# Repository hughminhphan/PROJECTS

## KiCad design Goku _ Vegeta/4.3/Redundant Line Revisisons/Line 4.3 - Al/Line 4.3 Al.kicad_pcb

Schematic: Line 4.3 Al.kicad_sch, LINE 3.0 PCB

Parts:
A1: ALS-PT19; R_1210_3225Metric; PARTREV 5
A2, A3, A4, A5, A6, A7, A8, A9, A10, A11, A12, A13, A14, A15, A16, A17, A18, A19, A20, A21, A22, A23, A24: ALS-PT19; XDCR_ALS-PT19-315C_L177_TR8; PARTREV 5
C1: 0.1uF; C_0402_1005Metric
C2: 10uF; 0805
C3: 4.7uF; C_0805_2012Metric
C4: 0.1uF; C_0805_2012Metric
C5, C6: 22uF; C_0805_2012Metric
C7: 1uF; C_0805_2012Metric
J1, J2, J3, J4: Solder Pad; SolderWirePad_1x01_SMD_1x2mm
LED1, LED2, LED3, LED4, LED5, LED6, LED7, LED8, LED9, LED10, LED11, LED12, LED13, LED14, LED15, LED16, LED17, LED18, LED19, LED20, LED21, LED22, LED23, LED24: JB2835AWT-W-U30GA0000-N0000001; LED_J2835_CRW
R1, R2, R3, R4, R5, R6, R7, R8, R9, R10, R11, R12, R13, R14, R15, R16, R17, R18, R19, R20, R21, R22, R23, R24: 12R; 0805
R25, R26, R27, R28, R29, R30, R31, R32, R33, R34, R35, R36, R37, R38, R39, R40, R41, R42, R43, R44, R45, R46, R47, R48: 330R; 0805
R49, R50, R51, R52, R53, R54, R55, R56, R57, R58, R59, R60, R61, R62, R63, R64, R65, R66, R67, R68, R69, R70, R71, R72, R97, R98, R99, R100, R101, R102, R103, R104, R105, R106, R107, R108: 10k; 0805
R73, R74, R75, R76, R77, R78, R79, R80, R81, R82, R83, R84, R85, R86, R87, R88, R89, R90, R91, R92, R93, R94, R95, R96, R133, R134, R135, R136, R137, R138, R139, R140, R141, R142, R143, R144, R145, R146, R147, R148, R149, R152, R153, R154, R155, R156: 0R; R_1210_3225Metric
R109, R110, R111, R112, R113, R114, R115, R116, R117, R118, R119, R120, R121, R122, R123, R124, R125, R126, R127, R128, R129, R130, R131, R132: 0R; R_0603_1608Metric
R150, R151: 10k; R_0805_2012Metric
R157: 0R; R_0805_2012Metric
U1, U2, U3, U4, U5, U6: LM339; TSSOP-14_W4.4mm
U7: SC0915; MODULE_SC0915; PARTREV 1.9
U8: TPSM33625RDNR; QFN-FCMOD11_RDN_TEX

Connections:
+3V3: A1.1, A2.1, A3.1, A4.1, A5.1, A6.1, A7.1, A8.1, A9.1, A10.1, A11.1, A12.1, A13.1, A14.1, A15.1, A16.1, A17.1, A18.1, A19.1, A20.1, A21.1, A22.1, A23.1, A24.1, C1.2, C2.2, C5.1, C6.1, R1.1, R2.1, R3.1, R4.1, R5.1, R6.1, R7.1, R8.1, R9.1, R10.1, R11.1, R12.1, R13.1, R14.1, R15.1, R16.1, R17.1, R18.1, R19.1, R20.1, R21.1, R22.1, R23.1, R24.1, R49.2, R50.2, R51.2, R52.2, R53.2, R54.2, R55.2, R56.2, R57.2, R58.2, R59.2, R60.2, R61.2, R62.2, R63.2, R64.2, R65.2, R66.2, R67.2, R68.2, R69.2, R70.2, R71.2, R72.2, R97.2, R99.2, R101.2, R103.2, R105.2, R107.2, R109.1, R109.2, R110.1, R110.2, R111.1, R111.2, R112.1, R112.2, R113.1, R113.2, R114.1, R114.2, R115.1, R115.2, R116.1, R116.2, R117.1, R117.2, R118.1, R118.2, R119.1, R119.2, R120.1, R120.2, R121.1, R121.2, R122.1, R122.2, R123.1, R123.2, R124.1, R124.2, R125.1, R125.2, R126.1, R126.2, R127.1, R127.2, R128.1, R128.2, R129.1, R129.2, R130.1, R130.2, R131.1, R131.2, R132.1, R132.2, R150.2, R152.1, R152.2, R153.1, R153.2, R154.1, R154.2, R155.1, R155.2, R156.1, R156.2, U1.3 (V+), U2.3 (V+), U3.3 (V+), U4.3 (V+), U5.3 (V+), U6.3 (V+), U7.39 (VSYS), U8.4 (VOUT)
+15V: C3.1, C4.1, J1.1, U8.2 (EN), U8.3 (VIN)
/SCL: J4.1, U7.2 (GP1)
/SDA: J3.1, U7.1 (GP0)
/SEN1: R49.1, U1.2, U7.29 (GP22)
/SEN2: R50.1, U1.1, U7.31 (GP26)
/SEN3: R51.1, U1.14, U7.32 (GP27)
/SEN4: R52.1, U1.13, U7.34 (GP28)
/SEN5: R53.1, U2.2, U7.6 (GP4)
/SEN6: R54.1, U2.1, U7.7 (GP5)
/SEN7: R55.1, U2.14, U7.5 (GP3)
/SEN8: R56.1, U2.13, U7.4 (GP2)
/SEN9: R57.1, U3.2, U7.9 (GP6)
/SEN10: R58.1, U3.1, U7.10 (GP7)
/SEN11: R59.1, U3.14, U7.11 (GP8)
/SEN12: R60.1, U3.13, U7.12 (GP9)
/SEN13: R61.1, U4.2, U7.14 (GP10)
/SEN14: R62.1, U4.1, U7.15 (GP11)
/SEN15: R63.1, U4.14, U7.16 (GP12)
/SEN16: R64.1, U4.13, U7.17 (GP13)
/SEN17: R65.1, U5.2, U7.19 (GP14)
/SEN18: R66.1, U5.1, U7.20 (GP15)
/SEN19: R67.1, U5.14, U7.22 (GP17)
/SEN20: R68.1, U5.13, U7.21 (GP16)
/SEN21: R69.1, U6.2, U7.24 (GP18)
/SEN22: R70.1, U6.1, U7.25 (GP19)
/SEN23: R71.1, U6.14, U7.26 (GP20)
/SEN24: R72.1, U6.13, U7.27 (GP21)
/VREF1: R97.1, R98.2, U1.4 (-), U1.6 (-), U1.8 (-), U1.10 (-)
/VREF2: R99.1, R100.2, U2.4 (-), U2.6 (-), U2.8 (-), U2.10 (-)
/VREF3: R101.1, R102.2, U3.4 (-), U3.6 (-), U3.8 (-), U3.10 (-)
/VREF4: R103.1, R104.2, U4.4 (-), U4.6 (-), U4.8 (-), U4.10 (-)
/VREF5: R105.1, R106.2, U5.4 (-), U5.6 (-), U5.8 (-), U5.10 (-)
/VREF6: R107.1, R108.2, U6.4 (-), U6.6 (-), U6.8 (-), U6.10 (-)
GND: C1.1, C2.1, C3.2, C4.2, C5.2, C6.2, C7.2, J2.1, LED1.1, LED2.1, LED3.1, LED4.1, LED5.1, LED6.1, LED7.1, LED8.1, LED9.1, LED10.1, LED11.1, LED12.1, LED13.1, LED14.1, LED15.1, LED16.1, LED17.1, LED18.1, LED19.1, LED20.1, LED21.1, LED22.1, LED23.1, LED24.1, R25.1, R26.1, R27.1, R28.1, R29.1, R30.1, R31.1, R32.1, R33.1, R34.1, R35.1, R36.1, R37.1, R38.1, R39.1, R40.1, R41.1, R42.1, R43.1, R44.1, R45.1, R46.1, R47.1, R48.1, R73.1, R73.2, R74.1, R74.2, R75.1, R75.2, R76.1, R76.2, R77.1, R77.2, R78.1, R78.2, R79.1, R79.2, R80.1, R80.2, R81.1, R81.2, R82.1, R82.2, R83.1, R83.2, R84.1, R84.2, R85.1, R85.2, R86.1, R86.2, R87.1, R87.2, R88.1, R88.2, R89.1, R89.2, R90.1, R90.2, R91.1, R91.2, R92.1, R92.2, R93.1, R93.2, R94.1, R94.2, R95.1, R95.2, R96.1, R96.2, R98.1, R100.1, R102.1, R104.1, R106.1, R108.1, R133.1, R133.2, R134.1, R134.2, R135.1, R135.2, R136.1, R136.2, R137.1, R137.2, R138.1, R138.2, R139.1, R139.2, R140.1, R140.2, R141.1, R141.2, R142.1, R142.2, R143.1, R143.2, R144.1, R144.2, R145.1, R145.2, R146.1, R146.2, R147.1, R147.2, R148.1, R148.2, R149.1, R149.2, R151.1, R157.1, R157.2, U1.12 (V-), U2.12 (V-), U3.12 (V-), U4.12 (V-), U5.12 (V-), U6.12 (V-), U7.3 (GND), U7.8 (GND), U7.13 (GND), U7.18 (GND), U7.23 (GND), U7.28 (GND), U7.33 (AGND), U7.38 (GND), U7.D2 (GND), U8.10 (GND), U8.11 (RT)
unnamed: LED1.2, R1.2
unnamed: LED2.2, R2.2
unnamed: LED3.2, R3.2
unnamed: LED4.2, R4.2
unnamed: LED5.2, R5.2
unnamed: LED6.2, R6.2
unnamed: LED7.2, R7.2
unnamed: LED8.2, R8.2
unnamed: LED9.2, R9.2
unnamed: LED10.2, R10.2
unnamed: LED11.2, R11.2
unnamed: LED12.2, R12.2
unnamed: LED13.2, R13.2
unnamed: LED14.2, R14.2
unnamed: LED15.2, R15.2
unnamed: LED16.2, R16.2
unnamed: LED17.2, R17.2
unnamed: LED18.2, R18.2
unnamed: LED19.2, R19.2
unnamed: LED20.2, R20.2
unnamed: LED21.2, R21.2
unnamed: LED22.2, R22.2
unnamed: LED23.2, R23.2
unnamed: LED24.2, R24.2
unnamed: A1.2, R25.2, U1.5 (+)
unnamed: A2.2, R26.2, U1.7 (+)
unnamed: A4.2, R28.2, U1.11 (+)
unnamed: A3.2, R27.2, U1.9 (+)
unnamed: A5.2, R29.2, U2.5 (+)
unnamed: A6.2, R30.2, U2.7 (+)
unnamed: A8.2, R32.2, U2.11 (+)
unnamed: A7.2, R31.2, U2.9 (+)
unnamed: A9.2, R33.2, U3.5 (+)
unnamed: A10.2, R34.2, U3.7 (+)
unnamed: A12.2, R36.2, U3.11 (+)
unnamed: A11.2, R35.2, U3.9 (+)
unnamed: A13.2, R37.2, U4.5 (+)
unnamed: A14.2, R38.2, U4.7 (+)
unnamed: A16.2, R40.2, U4.11 (+)
unnamed: A15.2, R39.2, U4.9 (+)
unnamed: A17.2, R41.2, U5.5 (+)
unnamed: A18.2, R42.2, U5.7 (+)
unnamed: A20.2, R44.2, U5.11 (+)
unnamed: A19.2, R43.2, U5.9 (+)
unnamed: A21.2, R45.2, U6.5 (+)
unnamed: A22.2, R46.2, U6.7 (+)
unnamed: A24.2, R48.2, U6.11 (+)
unnamed: A23.2, R47.2, U6.9 (+)
unnamed: R150.1, R151.2, U8.9 (FB)
unnamed: U8.5 (SW), U8.6 (SW)
unnamed: C7.1, U8.8 (VCC)

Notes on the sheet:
NOTES TO SELF
NEXT STEPS: MAYBE: Things that are being tested: - buck converter circuit - potentimeter voltage divider circuit - comparator circuit - leds on 3v3
SENSORS
TUNING
make sure that resistor is 1/4 watt
CONNECTORS
MCU
3V3 BUCK CONVERTER
COMPARATORS

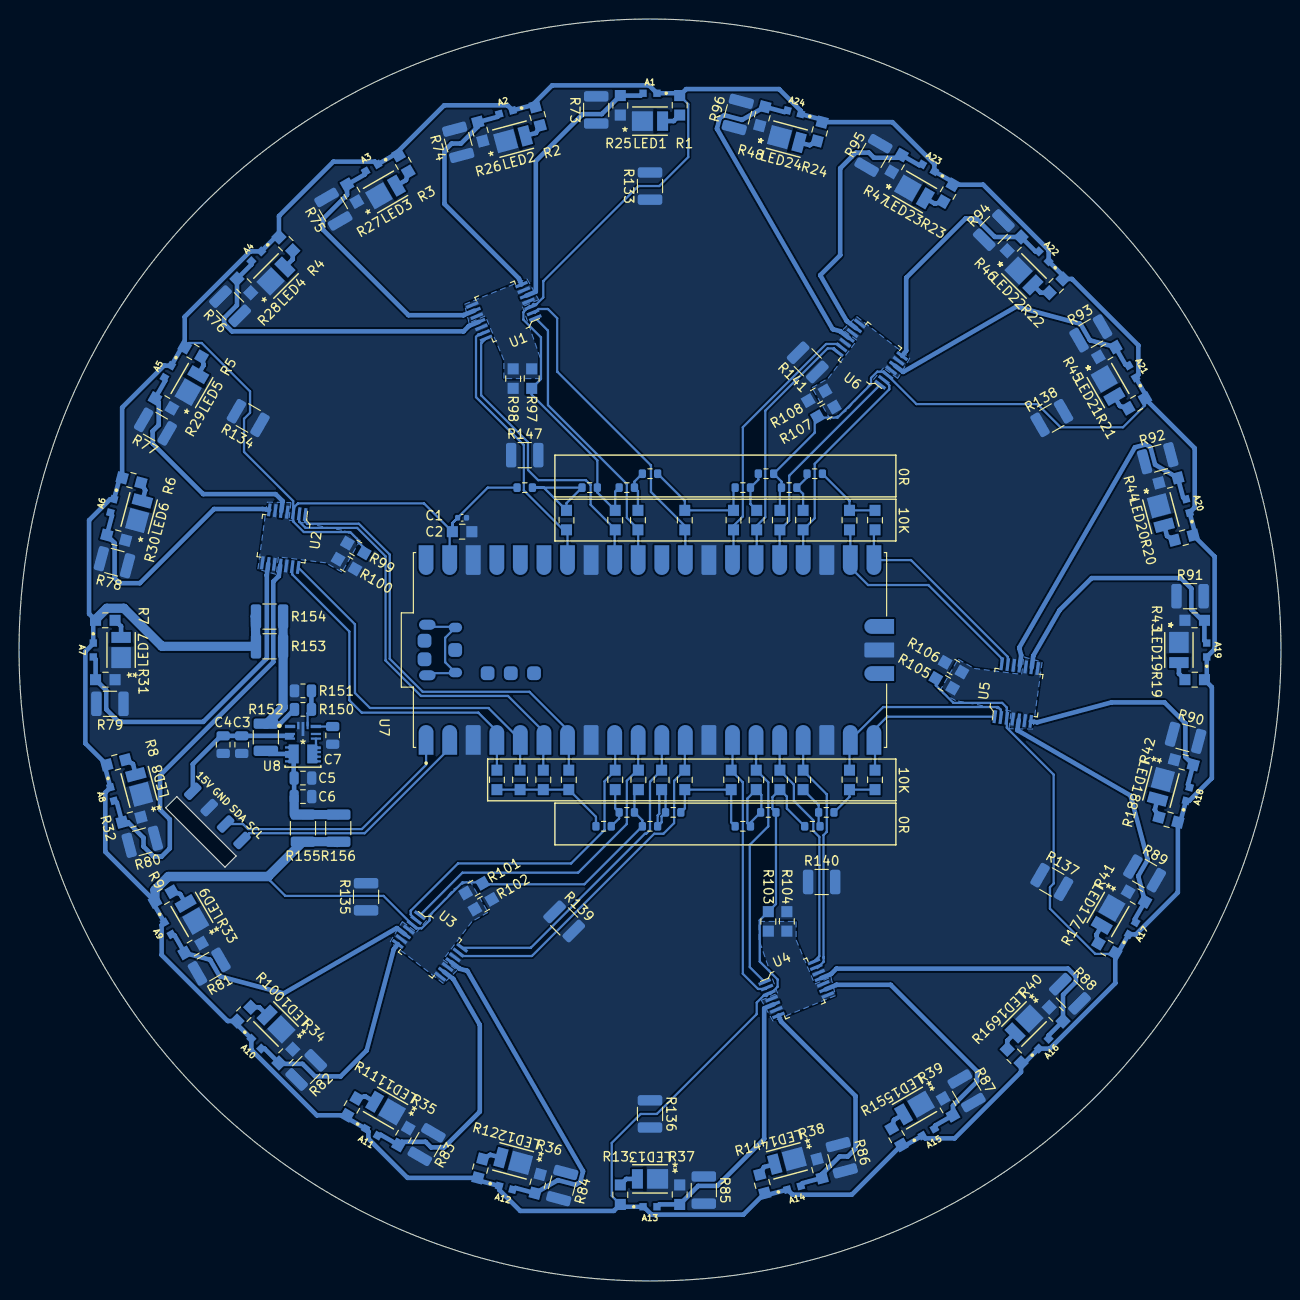
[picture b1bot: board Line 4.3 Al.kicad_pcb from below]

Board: 2 copper layers, 136.0 x 136.0 mm, 208 parts (208 on the bottom side), 86 nets.

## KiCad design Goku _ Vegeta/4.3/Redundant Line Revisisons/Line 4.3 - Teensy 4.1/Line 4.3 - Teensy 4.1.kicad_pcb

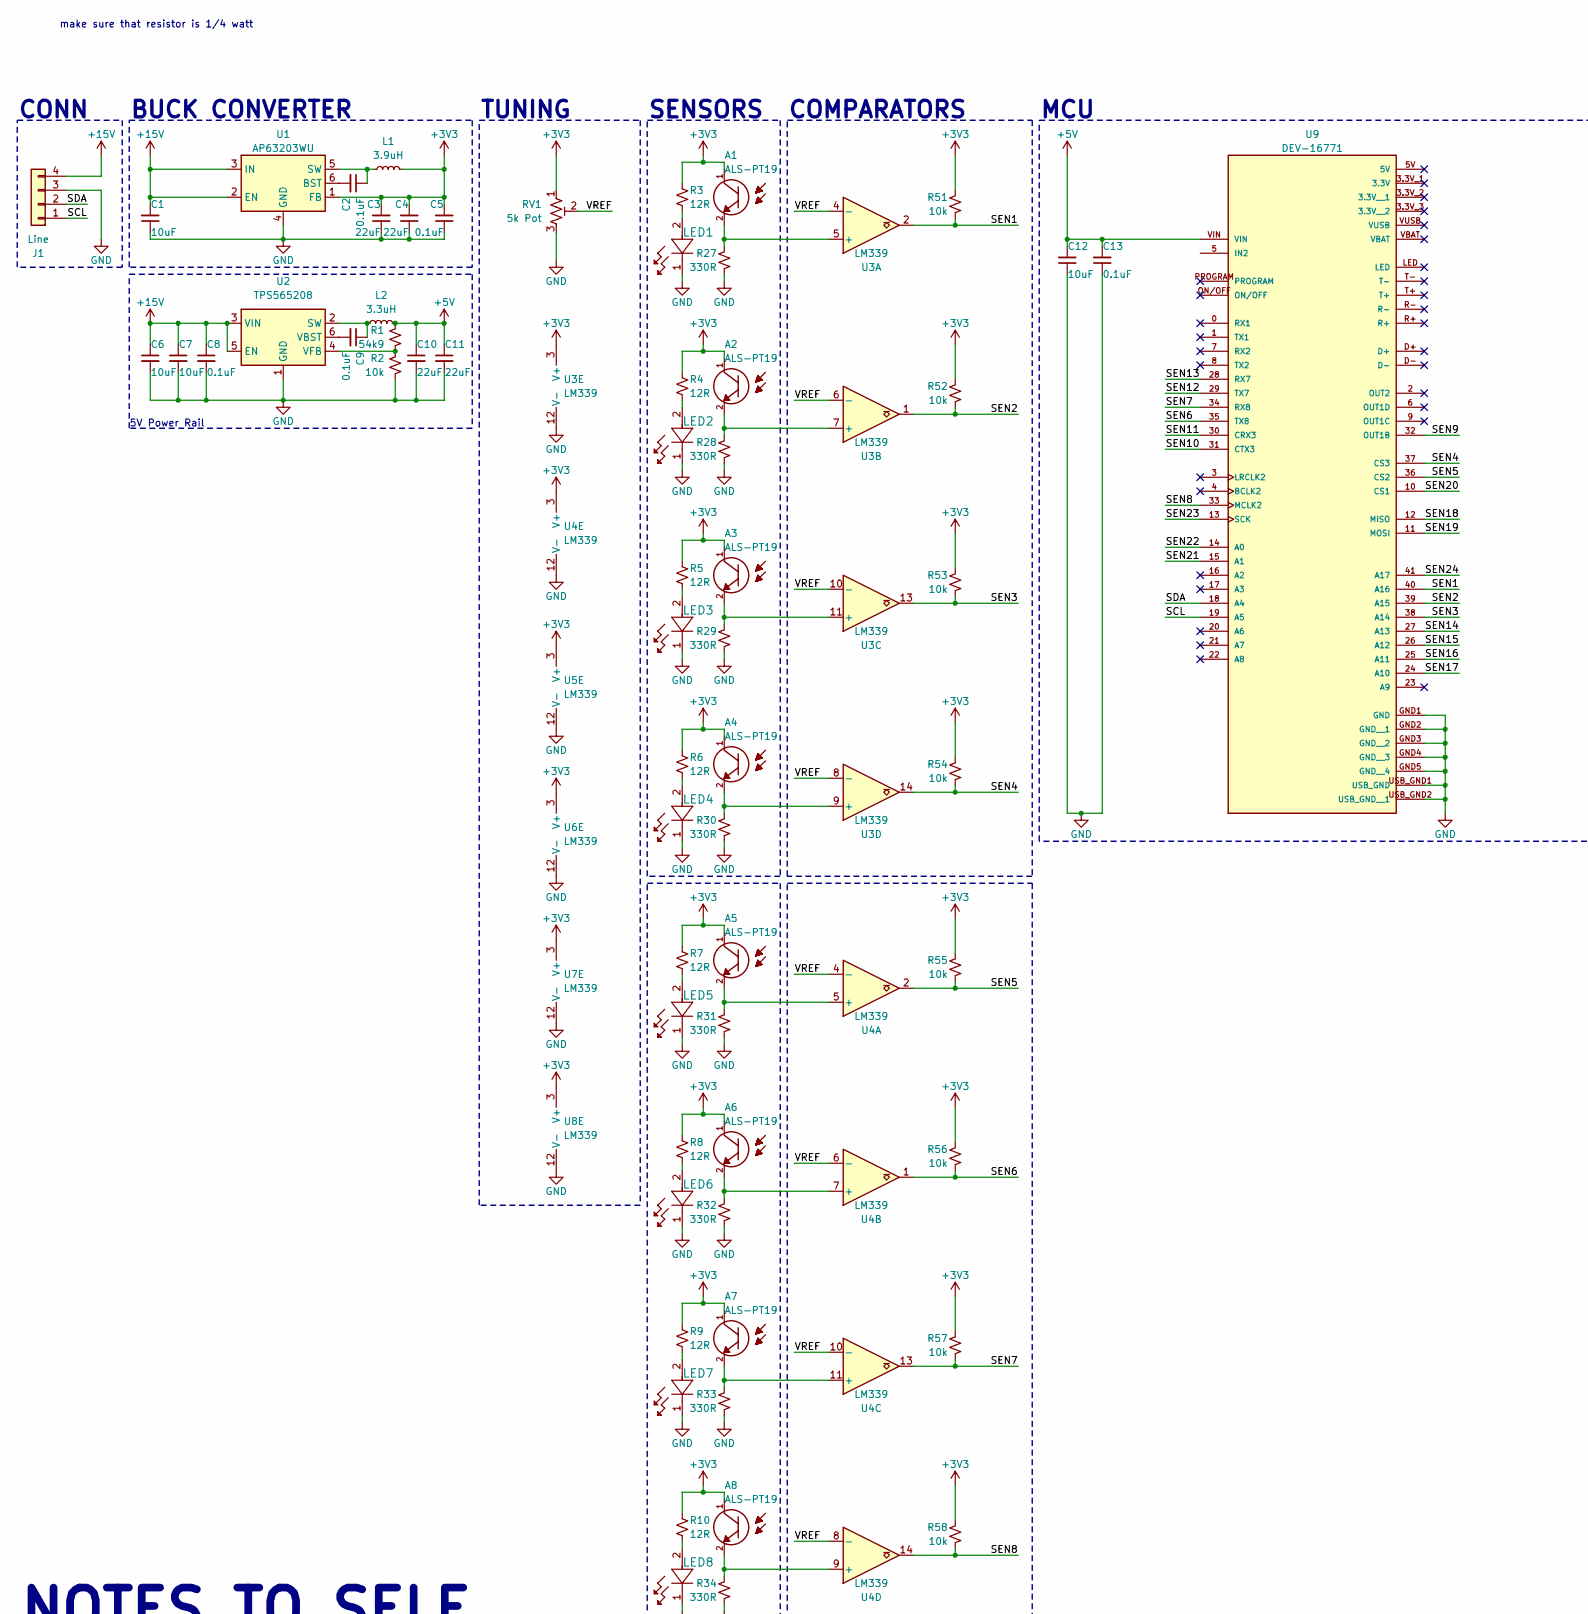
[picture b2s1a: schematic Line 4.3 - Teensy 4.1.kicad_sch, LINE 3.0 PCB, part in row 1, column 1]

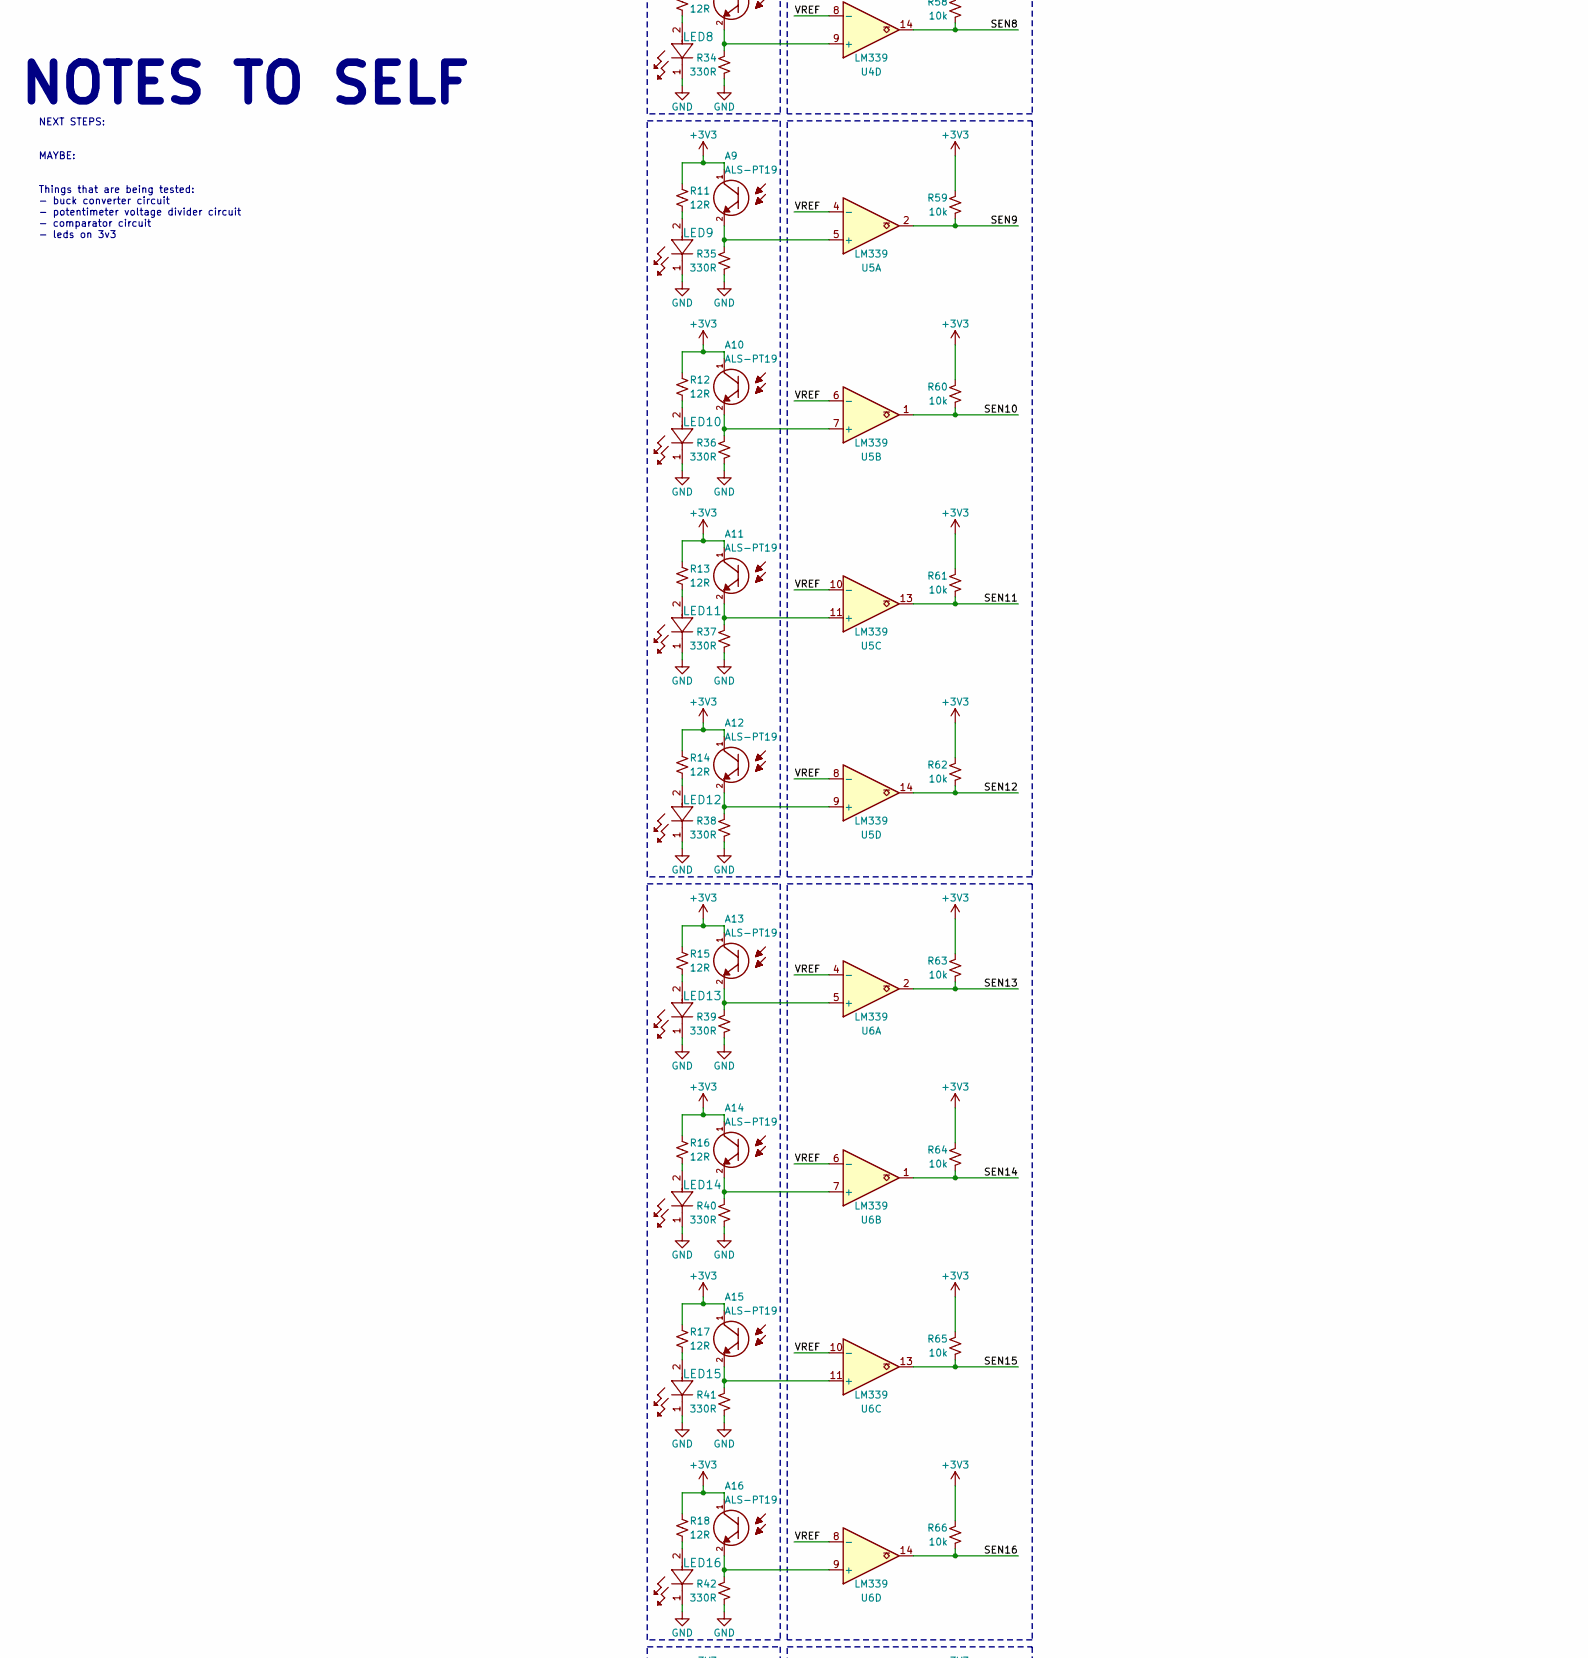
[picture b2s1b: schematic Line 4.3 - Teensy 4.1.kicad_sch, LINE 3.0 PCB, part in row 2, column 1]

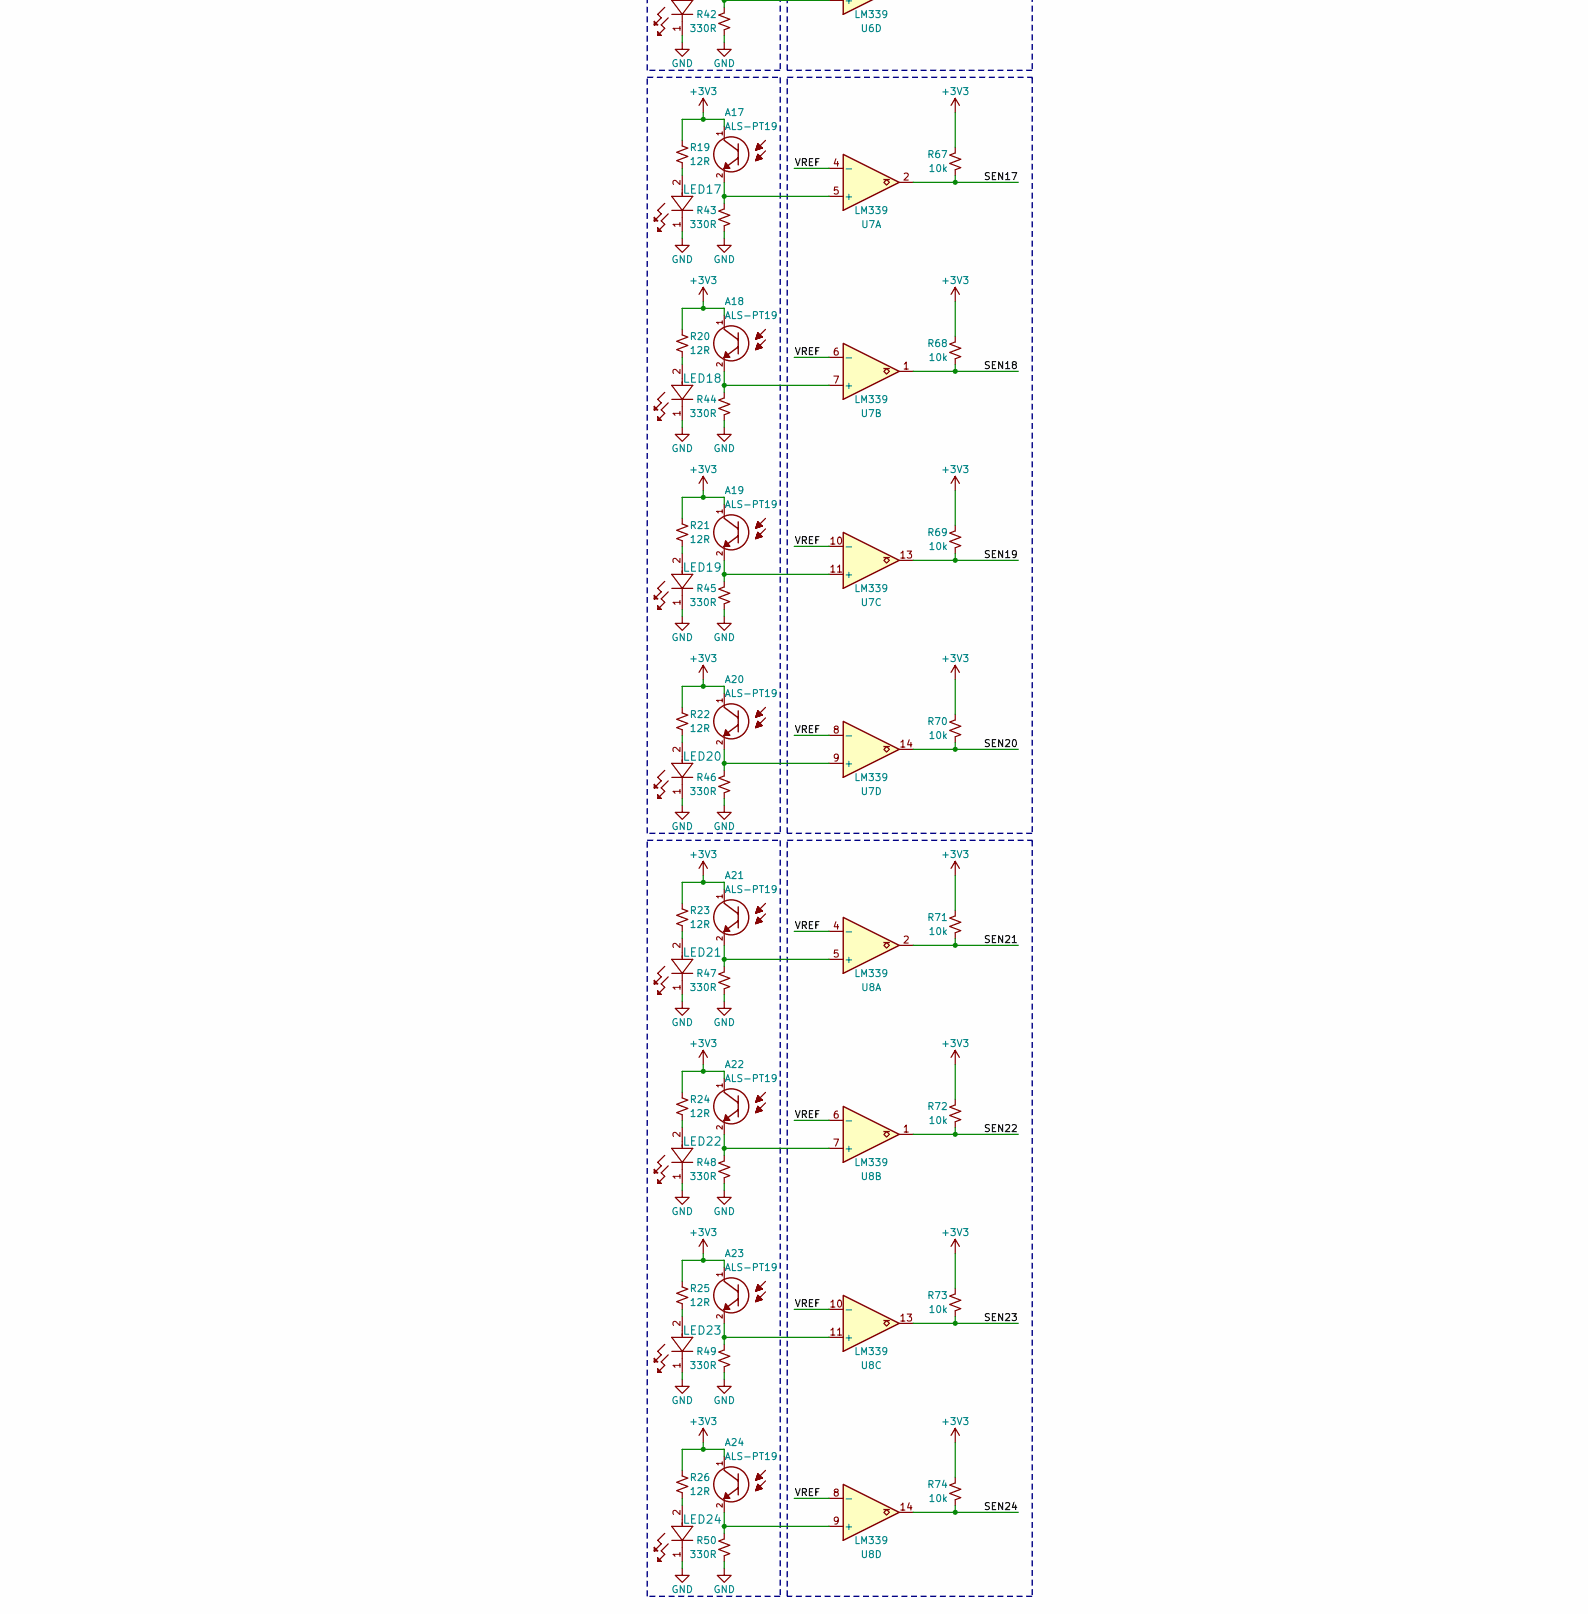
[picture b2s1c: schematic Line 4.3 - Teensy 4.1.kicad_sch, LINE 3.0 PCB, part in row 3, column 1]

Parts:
A1, A2, A3, A4, A5, A6, A7, A8, A9, A10, A11, A12, A13, A14, A15, A16, A17, A18, A19, A20, A21, A22, A23, A24: ALS-PT19; XDCR_ALS-PT19-315C_L177_TR8; PARTREV 5
C1, C6, C7, C12: 10uF; C_0805_2012Metric
C2, C5: 0.1uF; C_0805_2012Metric
C3, C4: 22uF; C_0805_2012Metric
C8, C9: 0.1uF; C_0603_1608Metric
C10, C11: 22uF; C_0603_1608Metric
C13: 0.1uF; C_0402_1005Metric
H1, H2, H3, H4: MountingHole; MountingHole_3.2mm_M3
J1: Line; JST_XH_B4B-XH-A_1x04_P2.50mm_Vertical
L1: 3.9uH; L_Bourns-SRU8043
L2: 3.3uH; MPXV1D0840
LED1, LED2, LED3, LED4, LED5, LED6, LED7, LED8, LED9, LED10, LED11, LED12, LED13, LED14, LED15, LED16, LED17, LED18, LED19, LED20, LED21, LED22, LED23, LED24: JB2835AWT-W-U30GA0000-N0000001; LED_J2835_CRW
R1: 54k9; R_0402_1005Metric
R2: 10k; R_0402_1005Metric
R3, R4, R5, R6, R7, R8, R9, R10, R11, R12, R13, R14, R15, R16, R17, R18, R19, R20, R21, R22, R23, R24, R25, R26: 12R; R_0805_2012Metric
R27, R28, R29, R30, R31, R32, R33, R34, R35, R36, R37, R38, R39, R40, R41, R42, R43, R44, R45, R46, R47, R48, R49, R50: 330R; R_0805_2012Metric
R51, R52, R53, R54, R55, R56, R57, R58, R59, R60, R61, R62, R63, R64, R65, R66, R67, R68, R69, R70, R71, R72, R73, R74: 10k; R_0805_2012Metric
RV1: 5k Pot; Potentiometer_Piher_PT-10-V10_Vertical
U1: AP63203WU; TSOT-23-6
U2: TPS565208; SOT-23-6
U3, U4, U5, U6, U7, U8: LM339; TSSOP-14_W4.4mm
U9: DEV-16771; MODULE_DEV-16771; PARTREV 4.1

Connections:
+3V3: A1.1, A2.1, A3.1, A4.1, A5.1, A6.1, A7.1, A8.1, A9.1, A10.1, A11.1, A12.1, A13.1, A14.1, A15.1, A16.1, A17.1, A18.1, A19.1, A20.1, A21.1, A22.1, A23.1, A24.1, C3.2, C4.2, C5.2, L1.2, R3.1, R4.1, R5.1, R6.1, R7.1, R8.1, R9.1, R10.1, R11.1, R12.1, R13.1, R14.1, R15.1, R16.1, R17.1, R18.1, R19.1, R20.1, R21.1, R22.1, R23.1, R24.1, R25.1, R26.1, R51.2, R52.2, R53.2, R54.2, R55.2, R56.2, R57.2, R58.2, R59.2, R60.2, R61.2, R62.2, R63.2, R64.2, R65.2, R66.2, R67.2, R68.2, R69.2, R70.2, R71.2, R72.2, R73.2, R74.2, RV1.1, U1.1 (FB), U3.3 (V+), U4.3 (V+), U5.3 (V+), U6.3 (V+), U7.3 (V+), U8.3 (V+)
+5V: C10.1, C11.1, C12.2, C13.2, L2.2, R1.1, U9.VIN
+15V: C1.2, C6.1, C7.1, C8.1, J1.4, U1.2 (EN), U1.3 (IN), U2.3 (VIN), U2.5 (EN)
/SCL: J1.1, U9.19 (A5)
/SDA: J1.2, U9.18 (A4)
/SEN1: R51.1, U3.2, U9.40 (A16)
/SEN2: R52.1, U3.1, U9.39 (A15)
/SEN3: R53.1, U3.13, U9.38 (A14)
/SEN4: R54.1, U3.14, U9.37 (CS3)
/SEN5: R55.1, U4.2, U9.36 (CS2)
/SEN6: R56.1, U4.1, U9.35 (TX8)
/SEN7: R57.1, U4.13, U9.34 (RX8)
/SEN8: R58.1, U4.14, U9.33 (MCLK2)
/SEN9: R59.1, U5.2, U9.32 (OUT1B)
/SEN10: R60.1, U5.1, U9.31 (CTX3)
/SEN11: R61.1, U5.13, U9.30 (CRX3)
/SEN12: R62.1, U5.14, U9.29 (TX7)
/SEN13: R63.1, U6.2, U9.28 (RX7)
/SEN14: R64.1, U6.1, U9.27 (A13)
/SEN15: R65.1, U6.13, U9.26 (A12)
/SEN16: R66.1, U6.14, U9.25 (A11)
/SEN17: R67.1, U7.2, U9.24 (A10)
/SEN18: R68.1, U7.1, U9.12 (MISO)
/SEN19: R69.1, U7.13, U9.11 (MOSI)
/SEN20: R70.1, U7.14, U9.10 (CS1)
/SEN21: R71.1, U8.2, U9.15 (A1)
/SEN22: R72.1, U8.1, U9.14 (A0)
/SEN23: R73.1, U8.13, U9.13 (SCK)
/SEN24: R74.1, U8.14, U9.41 (A17)
/VREF: RV1.2, U3.4 (-), U3.6 (-), U3.8 (-), U3.10 (-), U4.4 (-), U4.6 (-), U4.8 (-), U4.10 (-), U5.4 (-), U5.6 (-), U5.8 (-), U5.10 (-), U6.4 (-), U6.6 (-), U6.8 (-), U6.10 (-), U7.4 (-), U7.6 (-), U7.8 (-), U7.10 (-), U8.4 (-), U8.6 (-), U8.8 (-), U8.10 (-)
GND: C1.1, C3.1, C4.1, C5.1, C6.2, C7.2, C8.2, C10.2, C11.2, C12.1, C13.1, J1.3, LED1.1, LED2.1, LED3.1, LED4.1, LED5.1, LED6.1, LED7.1, LED8.1, LED9.1, LED10.1, LED11.1, LED12.1, LED13.1, LED14.1, LED15.1, LED16.1, LED17.1, LED18.1, LED19.1, LED20.1, LED21.1, LED22.1, LED23.1, LED24.1, R2.2, R27.1, R28.1, R29.1, R30.1, R31.1, R32.1, R33.1, R34.1, R35.1, R36.1, R37.1, R38.1, R39.1, R40.1, R41.1, R42.1, R43.1, R44.1, R45.1, R46.1, R47.1, R48.1, R49.1, R50.1, RV1.3, U1.4 (GND), U2.1 (GND), U3.12 (V-), U4.12 (V-), U5.12 (V-), U6.12 (V-), U7.12 (V-), U8.12 (V-), U9.GND1 (GND), U9.GND2 (GND__1), U9.GND3 (GND__2), U9.GND4 (GND__3), U9.GND5 (GND__4), U9.USB_GND1 (USB_GND), U9.USB_GND2 (USB_GND__1)
unnamed: LED1.2, R3.2
unnamed: LED2.2, R4.2
unnamed: LED3.2, R5.2
unnamed: LED4.2, R6.2
unnamed: LED5.2, R7.2
unnamed: LED6.2, R8.2
unnamed: LED7.2, R9.2
unnamed: LED8.2, R10.2
unnamed: LED9.2, R11.2
unnamed: LED10.2, R12.2
unnamed: LED11.2, R13.2
unnamed: LED12.2, R14.2
unnamed: LED13.2, R15.2
unnamed: LED14.2, R16.2
unnamed: LED15.2, R17.2
unnamed: LED16.2, R18.2
unnamed: LED17.2, R19.2
unnamed: LED18.2, R20.2
unnamed: LED19.2, R21.2
unnamed: LED20.2, R22.2
unnamed: LED21.2, R23.2
unnamed: LED22.2, R24.2
unnamed: LED23.2, R25.2
unnamed: LED24.2, R26.2
unnamed: C2.2, U1.6 (BST)
unnamed: C2.1, L1.1, U1.5 (SW)
unnamed: C9.1, L2.1, U2.2 (SW)
unnamed: C9.2, U2.6 (VBST)
unnamed: R1.2, R2.1, U2.4 (VFB)
unnamed: A1.2, R27.2, U3.5 (+)
unnamed: A2.2, R28.2, U3.7 (+)
unnamed: A3.2, R29.2, U3.11 (+)
unnamed: A4.2, R30.2, U3.9 (+)
unnamed: A5.2, R31.2, U4.5 (+)
unnamed: A6.2, R32.2, U4.7 (+)
unnamed: A7.2, R33.2, U4.11 (+)
unnamed: A8.2, R34.2, U4.9 (+)
unnamed: A9.2, R35.2, U5.5 (+)
unnamed: A10.2, R36.2, U5.7 (+)
unnamed: A11.2, R37.2, U5.11 (+)
unnamed: A12.2, R38.2, U5.9 (+)
unnamed: A13.2, R39.2, U6.5 (+)
unnamed: A14.2, R40.2, U6.7 (+)
unnamed: A15.2, R41.2, U6.11 (+)
unnamed: A16.2, R42.2, U6.9 (+)
unnamed: A17.2, R43.2, U7.5 (+)
unnamed: A18.2, R44.2, U7.7 (+)
unnamed: A19.2, R45.2, U7.11 (+)
unnamed: A20.2, R46.2, U7.9 (+)
unnamed: A21.2, R47.2, U8.5 (+)
unnamed: A22.2, R48.2, U8.7 (+)
unnamed: A23.2, R49.2, U8.11 (+)
unnamed: A24.2, R50.2, U8.9 (+)

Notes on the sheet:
NOTES TO SELF
NEXT STEPS: MAYBE: Things that are being tested: - buck converter circuit - potentimeter voltage divider circuit - comparator circuit - leds on 3v3
SENSORS
TUNING
make sure that resistor is 1/4 watt
CONN
MCU
BUCK CONVERTER
5V Power Rail
COMPARATORS

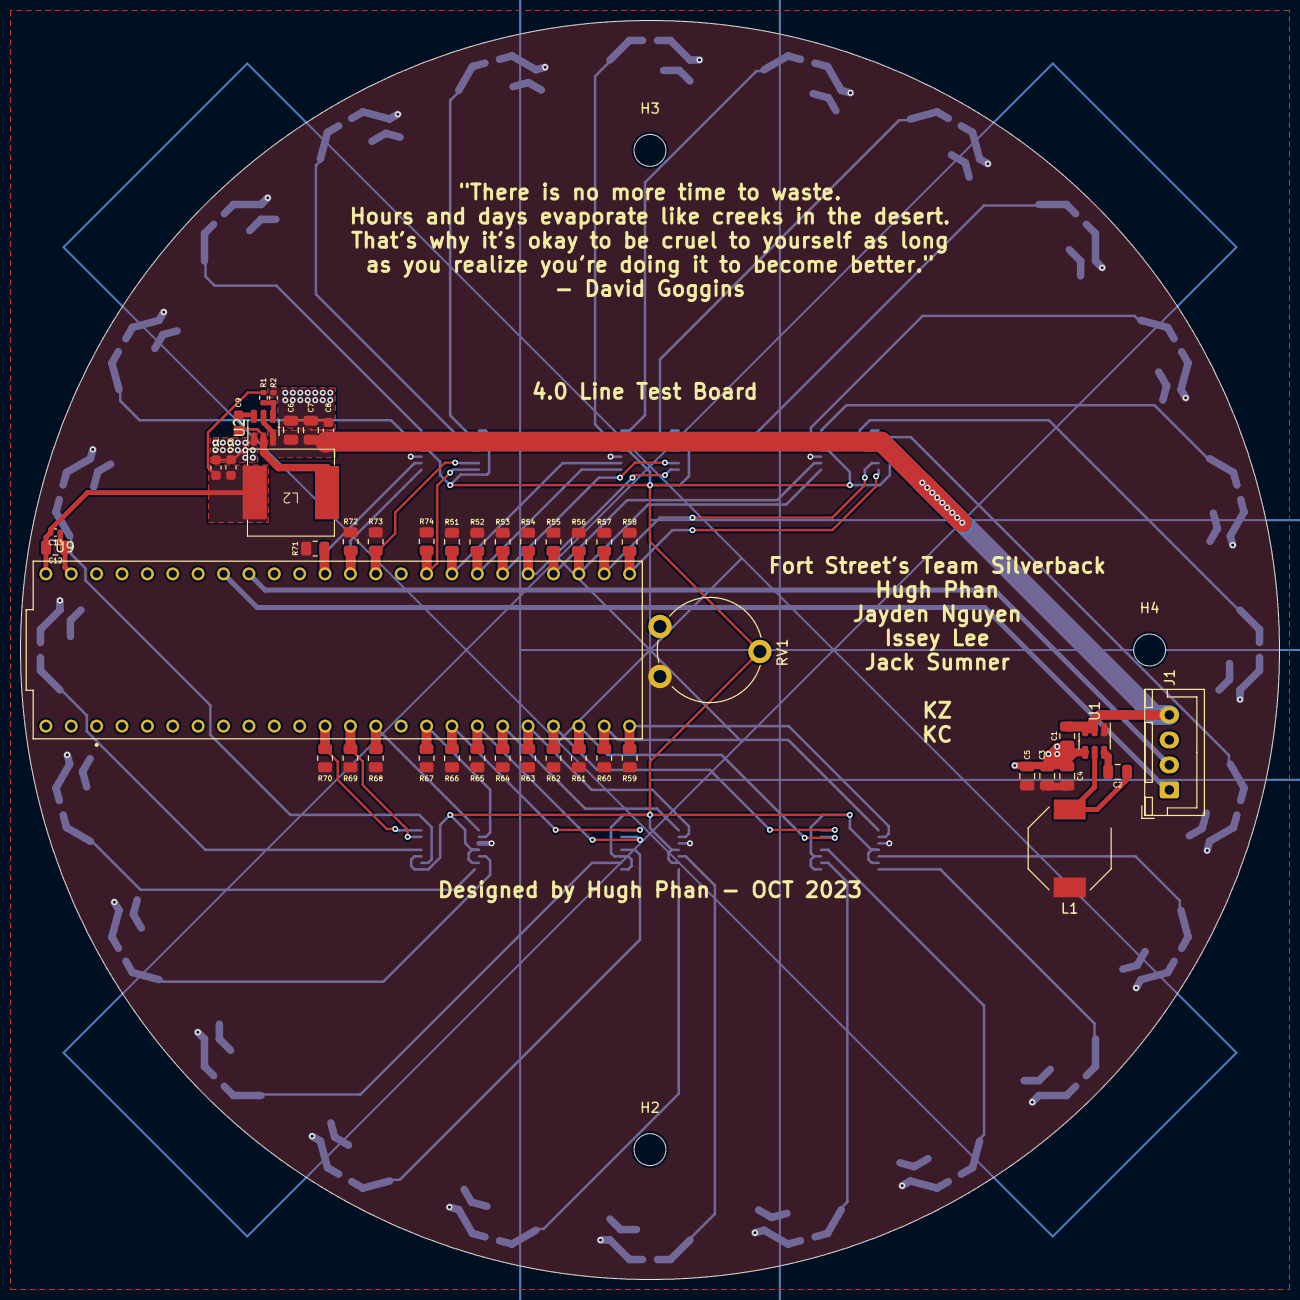
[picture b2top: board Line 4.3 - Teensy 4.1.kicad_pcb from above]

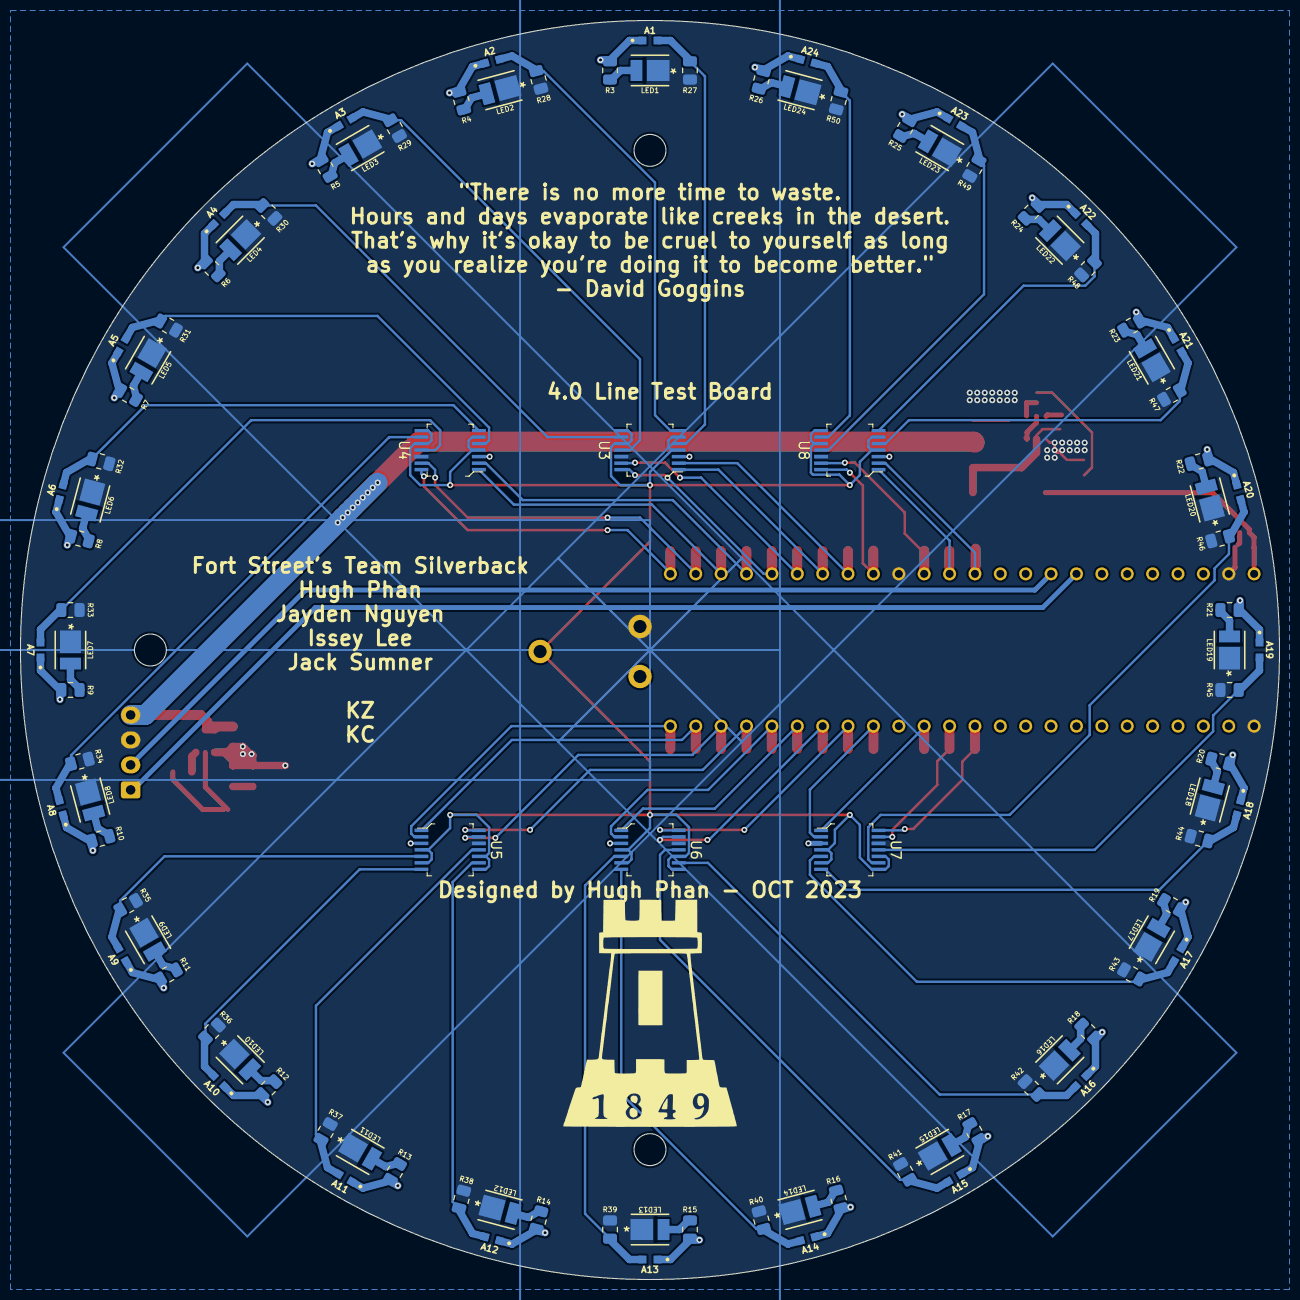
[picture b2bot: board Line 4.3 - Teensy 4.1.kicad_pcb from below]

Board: 2 copper layers, 126.0 x 126.0 mm, 151 parts (102 on the bottom side), 84 nets.
